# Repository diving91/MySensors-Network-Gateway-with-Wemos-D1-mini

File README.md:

# MySensors-Network-Gateway-with-Wemos-D1-mini
WiFi Gateway for MySensors network

Arduino sketch and PCB for an ESP8266 based WiFi Gateway for MySensors network (NRF24)</br>
It uses a Wemos D1 mini and a NRF24L01+ module boards</br>
It uses a mains power supply

It fits perfectly in a small and low cost enclosure from  SUPERTRONIC reference PP73N :</br>
http://www.tme.eu/fr/details/pp73n/boitiers-dappar-dalarme-et-de-capt/supertronic/

Note that in this PCB the Wemos module is mounted with</br>
-ESP WiFi module bottom side</br>
-CH340 & USB upper side</br>
This is the opposite side of common usage, but it greatly ease the use of the USB connector</br>
This is easily done since the Wemos D1 mini module comes with unsoldered breakout pins</br>
Take care when soldering the wemos D1 mini's breakout pins to solder them accordingly to the PCB layout of this repository</br>

<b>Mounting view</b></br>
     CH340 USB driver</br>
-----Wemos PCB-----</br>
        WiFi module</br>
---------- PCB ----------</br>

See also in Pictures folder</br>

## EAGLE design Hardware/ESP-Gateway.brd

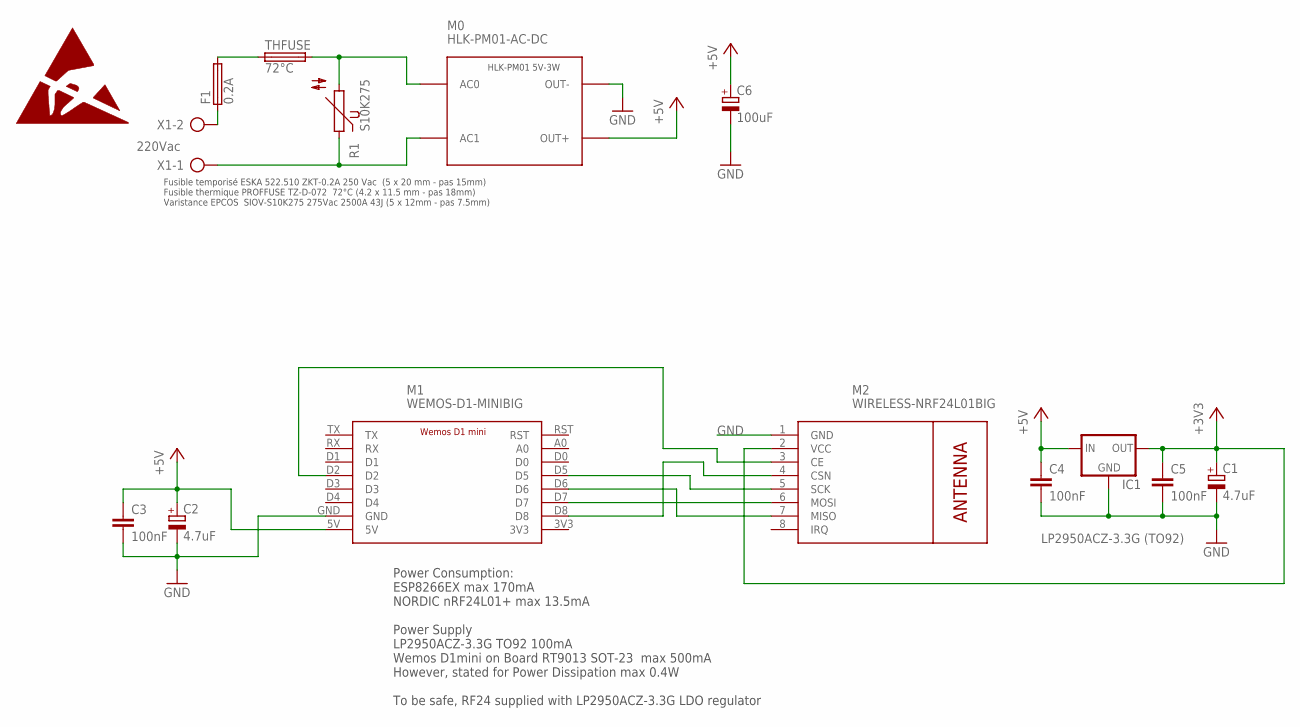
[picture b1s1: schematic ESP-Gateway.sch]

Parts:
C1, C2: 4.7uF; E2-5@1
C3, C4, C5: 100nF; C2.5-4
C6: 100uF; E3-8
F1: 0.2A; PTF75
IC1: LP2950ACZ-3.3G (TO92); DC-DC-TO92L
M0: HLK-PM01-AC-DC
M1: WEMOS-D1-MINIBIG; WEMOS-D1-MINI-DIY
M2: WIRELESS-NRF24L01BIG; WIRELESS-NRF24L01-DIY
R1: S10K275
THFUSE: 72°C; PROFFUSE-TZ-D
X1: 220Vac; DG301-5.0

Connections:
3V3: M1.3V3
+3V3: C1.+, C5.1, IC1.OUT, M2.2 (VCC)
+5V: C2.+, C3.1, C4.1, C6.+, IC1.IN, M0.OUT+, M1.5V
CE: M1.D2, M2.3 (CE)
CSN: M1.D8, M2.4 (CSN)
GND: C1.-, C2.-, C3.2, C4.2, C5.2, C6.-, IC1.GND, M0.OUT-, M1.GND, M2.1 (GND)
MISO: M1.D6, M2.7 (MISO)
MOSI: M1.D7, M2.6 (MOSI)
unnamed: M0.AC1, R1.1, X1.1
unnamed: F1.2, THFUSE.1
unnamed: F1.1, X1.2
unnamed: M0.AC0, R1.2, THFUSE.2
SCK: M1.D5, M2.5 (SCK)

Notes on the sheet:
Fusible temporisé ESKA 522.510 ZKT-0.2A 250 Vac (5 x 20 mm - pas 15mm) Fusible thermique PROFFUSE TZ-D-072 72°C (4.2 x 11.5 mm - pas 18mm) Varistance EPCOS SIOV-S10K275 275Vac 2500A 43J (5 x 12mm - pas 7.5mm)
Power Consumption: ESP8266EX max 170mA NORDIC nRF24L01+ max 13.5mA Power Supply LP2950ACZ-3.3G TO92 100mA Wemos D1mini on Board RT9013 SOT-23 max 500mA However, stated for Power Dissipation max 0.4W To be safe, RF24 supplied with LP2950ACZ-3.3G LDO regulator

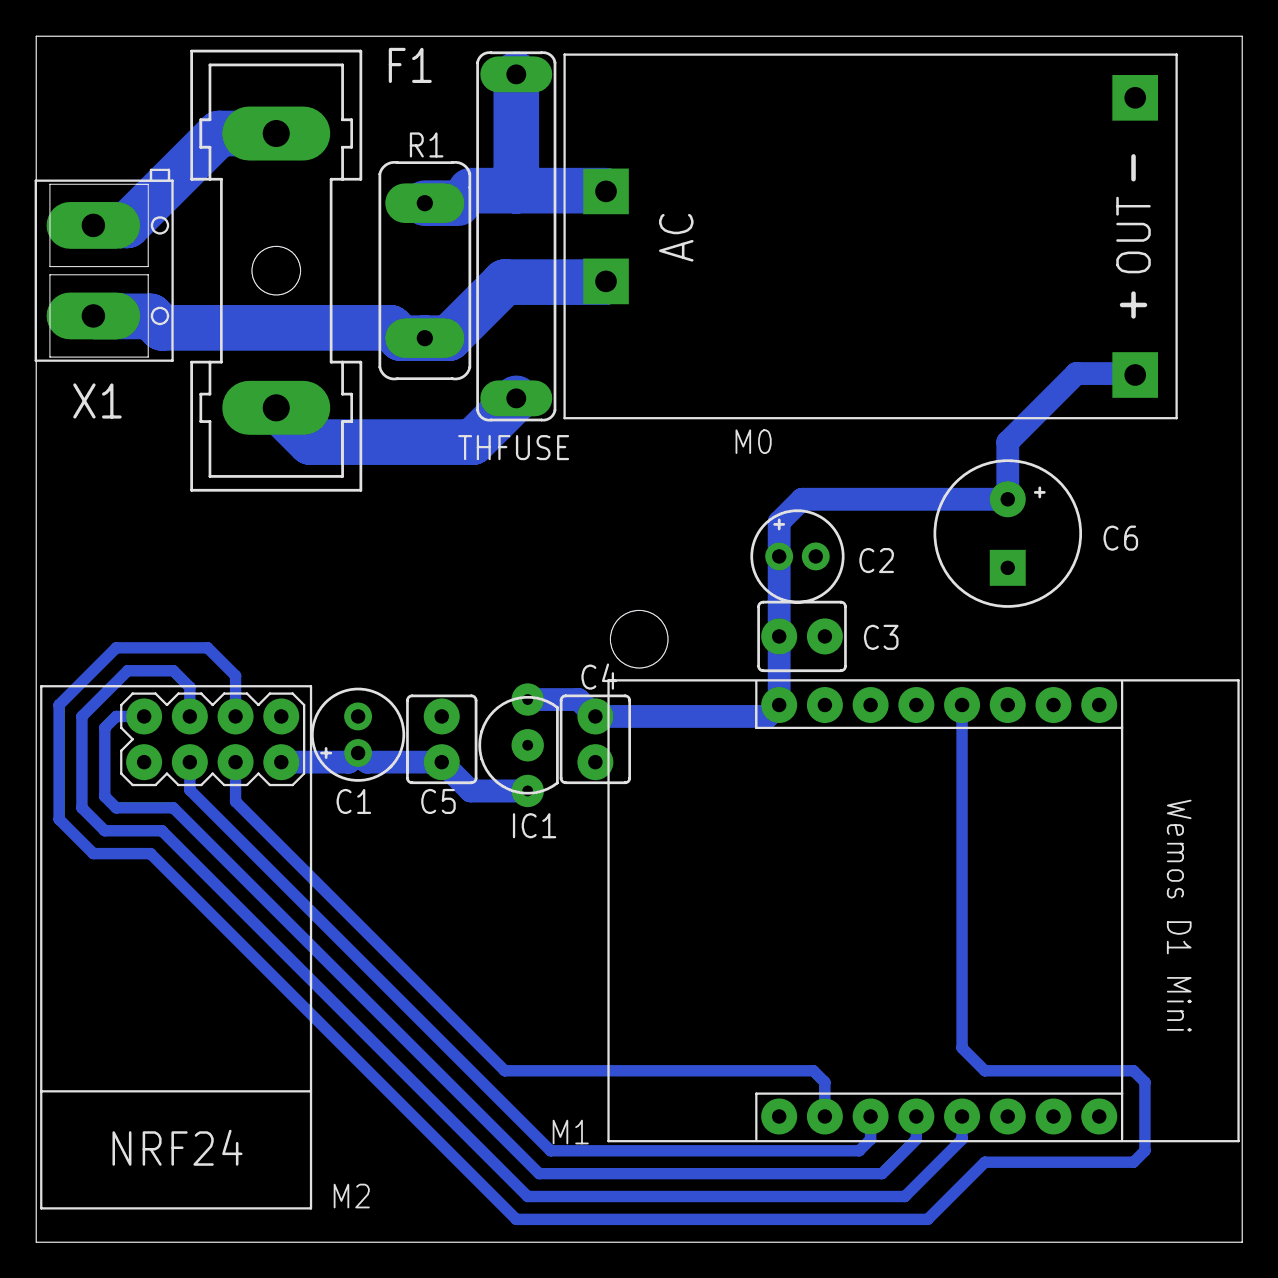
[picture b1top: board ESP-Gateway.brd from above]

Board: 1 copper layer, 67.0 x 67.0 mm, 15 parts (0 on the bottom side), 12 nets.

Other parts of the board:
DRILEGEND: DRILEGEND

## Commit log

2016-05-06 Added files via upload
2016-05-06 Node Schematics
2016-05-06 PCB Layout
2016-05-06 Add PCB Layout
2016-05-06 Add PCB view from copper side
2016-05-06 Add Eagle 7.5.0 sch file
2016-05-06 Add Eagle 7.5.0 brd file
2016-05-06 Mounting photos

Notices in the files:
parts and their libraries:
SparkFun-Aesthetics: Licensing: Creative Commons ShareAlike 4.0 International - https://creativecommons.org/licenses/by-sa/4.0
